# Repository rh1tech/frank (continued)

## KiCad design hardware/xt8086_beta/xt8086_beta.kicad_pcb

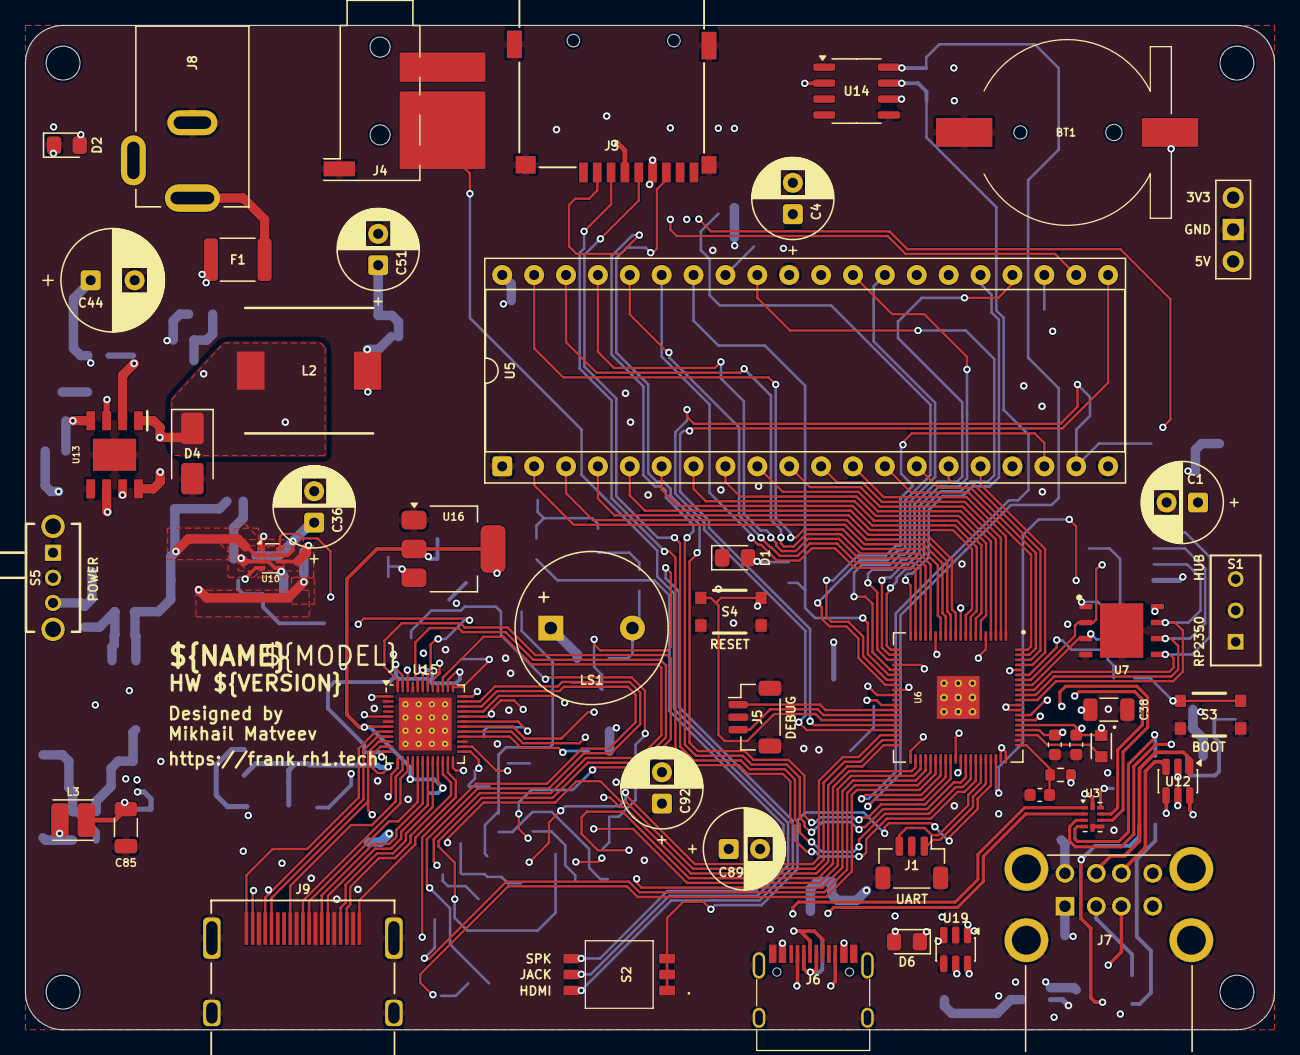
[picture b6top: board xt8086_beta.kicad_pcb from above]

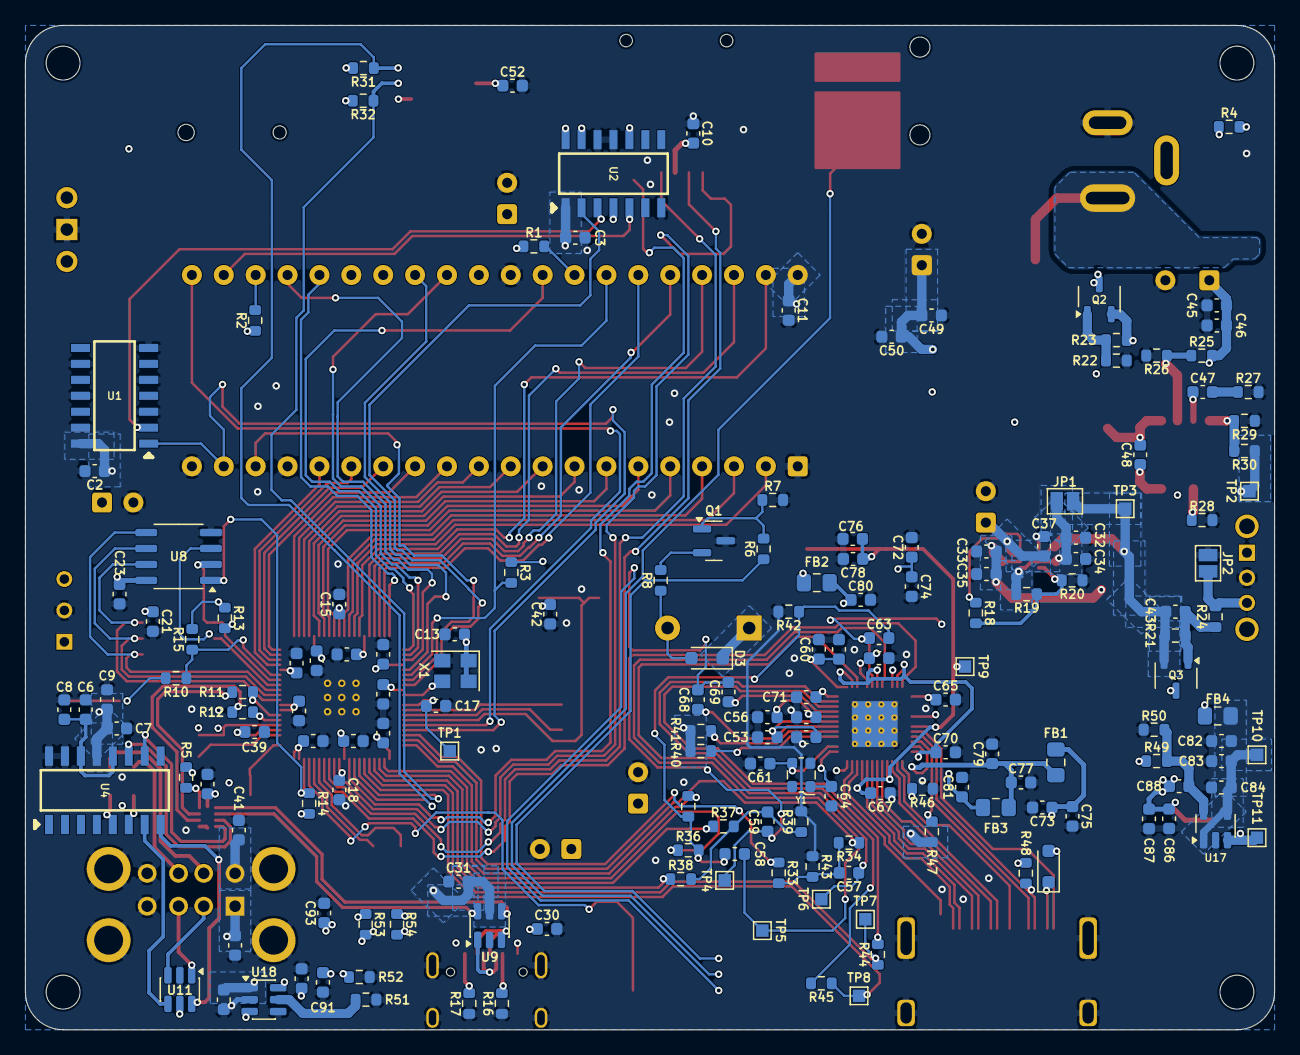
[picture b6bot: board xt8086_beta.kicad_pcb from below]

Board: 4 copper layers, 99.5 x 80.0 mm, 219 parts (167 on the bottom side), 163 nets.

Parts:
BT1: Battery_CR1220
C1, C4, C36, C89, C92: 100u; CP_Radial_D6.3mm_P2.50mm
C2, C3, C5, C8, C9, C10, C11, C13, C15, C18, C19, C20, C21, C22, C23, C24, C25, C26, C27, C28, C29, C30, C31, C32, C33, C37, C39, C46, C48, C49, C52, C57, C58, C59, C65, C66, C67, C70, C71, C74, C75, C84, C87, C93, C94: 100n; C_0603_1608Metric
C6, C43, C68, C69, C78, C79: 1u; C_0603_1608Metric
C7, C12, C14, C16, C17, C54, C56, C62: 4.7u; C_0603_1608Metric
C34, C35, C40, C41, C45, C50, C72, C73, C76, C77, C80, C81, C82, C83, C86, C90, C91: 10u; C_0603_1608Metric
C38, C85: 100u; C_1206_3216Metric
C42, C63: 1n; C_0603_1608Metric
C44: 680u; CP_Radial_D8.0mm_P3.50mm
C47: 150p; C_0603_1608Metric
C51: 220u; CP_Radial_D6.3mm_P2.50mm
C53, C55, C60: 220n; C_0603_1608Metric
C61, C64: 15p; C_0603_1608Metric
C88: 22p; C_0603_1608Metric
D1, D6: Red; LED_0805_2012Metric_Pad1.15x1.40mm_HandSolder
D2: Green; LED_0805_2012Metric_Pad1.15x1.40mm_HandSolder
D3: 1N4148; D_SOD-323
D4: SS34; D_SMA
D5: 1N5819WS; D_SOD-323
F1: 1.5A 24V; Fuse_1812_4532Metric
FB1, FB2, FB3: 220R; L_0805_2012Metric
FB4: 330R 2A; L_0805_2012Metric
H1, H2, H3, H4: Hole 2.7mm; MountingHole_2.7mm
J1: UART; JST_SH_1x03_P1.00mm_Vertical
J2: PWR; PinHeader_1x03_P2.54mm_Vertical
J3: 104031-0811; MicroSD_SMD_Long
J4: PJ-320D; AudioJack_3.5mm_PJ320D_AudioOut
J5: Debug; JST_SH_1x03_P1.00mm_Vertical
J6: USB4215-03-A; USB_C_Receptacle
J7: SS-52100-004; USB_A_Stacked
J8: DC-005-5A-2.0; BarrelJack_DC-005
J9: DC3RX19JA2; HDMI_Female
JP1: Power Debug; SolderJumper-2_P1.3mm_Open_Pad1.0x1.5mm
JP2: Force On; SolderJumper-2_P1.3mm_Open_Pad1.0x1.5mm
L1: 3.3u; L_LQH2MCN100K02L
L2: 22uH; Inductor_CDRH104RNP
L3: 2.2uH; L_Cenker_CKCS3015
LS1: Buzzer; Buzzer_12x8.5RM6.5
Q1: BC847; SOT-23
Q2, Q3: AO3401A; SOT-23-3L_AOS
R1, R2, R3, R4, R10, R46, R54: 1K; R_0603_1608Metric
R5, R7, R13, R14, R24: 10K; R_0603_1608Metric
R6, R15: 0R; R_0603_1608Metric
R8: 22R; R_0603_1608Metric
R9: 33R; R_0603_1608Metric
R11, R12: 27R; R_0603_1608Metric
R16, R17: 5.1K; R_0603_1608Metric
R18: 1M; R_0603_1608Metric
R19: 300K; R_0603_1608Metric
R20, R21, R22, R23, R25, R27, R28, R49, R51, R52, R53: 100K; R_0603_1608Metric
R26: 39K; R_0603_1608Metric
R29: 8.2K; R_0603_1608Metric
R30: 43K; R_0603_1608Metric
R31, R32, R40, R41: 4.7K; R_0603_1608Metric
R33, R35, R37: 800R; R_0603_1608Metric
R34, R36, R38: 400R; R_0603_1608Metric
R39, R42, R43: 75R; R_0603_1608Metric
R44, R45: 100R; R_0603_1608Metric
R47, R48: 2K; R_0603_1608Metric
R50: 22K; R_0603_1608Metric
S1: SS12D00; Switch_Slide_SS12D00
S2: DS05-127-2-03BK-SMT-TR; SW_DIP_DS05-127-2-03BK-SMT
S3: Boot; Button_SMD_3x4x2mm
S4: Reset; Button_SMD_3x4x2mm
S5: SK12D07VG3NS; Switch_Slide_SK12D07VG3NS
TP1: +1V1; TestPoint_Pad_1.0x1.0mm
TP2: +5V_DC; TestPoint_Pad_1.0x1.0mm
TP3: +5V_SEL; TestPoint_Pad_1.0x1.0mm
TP4: R; TestPoint_Pad_1.0x1.0mm
TP5: G; TestPoint_Pad_1.0x1.0mm
TP6: B; TestPoint_Pad_1.0x1.0mm
TP7: HS; TestPoint_Pad_1.0x1.0mm
TP8: VS; TestPoint_Pad_1.0x1.0mm
TP9: AMS_1V8; TestPoint_Pad_1.0x1.0mm
TP10: +5V_BUCK; TestPoint_Pad_1.0x1.0mm
TP11: LX; TestPoint_Pad_1.0x1.0mm
U1: SN74LS04; SOIC127P600X175-14N
U2: SN74LS74; SOIC127P600X175-14N
U3: TS3USB221RSER; Texas_R-PUQFN-N10
U4: MW7211A; SOIC127P600X175-16N
U5: 8086_Min_Mode; DIP-40_W15.24mm_Socket
U6: RP2350B; RP2350-QFN-80_10x10_P0.4mm
U7: W25Q128JVPIQ; SON127P600X500X80-9N-D
U8: ESP-PSRAM64H; SO-8
U9, U11, U12: USBLC6-2SC6; SOT-23-6
U10: TPS2116DRL; SOT-583-8
U13: MP1584EN-LF-Z; SOIC-9_P1.27mm
U14: DS3231MZ; SO-8
U15: MS9288A; QFN-48_7x7mm_P0.4mm
U16: AMS1117-1.8; SOT-223-3_TabPin2
U17: SY8089AAAC; SOT-23-5
U18, U19: CH217K; SOT-23-6
X1: ASE-12MHz; Oscillator_SMD_3225_4Pin
Y1: 24.576 MHz; Crystal_SMD_2520-4Pin

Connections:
+1V1: C14.1, C15.1, C17.1, C18.1, L1.1, TP1.1 (1_1), U6.10 (DVDD), U6.32 (DVDD), U6.51 (DVDD), U6.65 (VREG_FB)
+3V3: C5.2, C10.2, C12.1, C13.1, C19.1, C20.1, C21.1, C22.1, C23.1, C24.1, C25.1, C26.1, C27.1, C28.1, C29.1, C38.1, C39.1, C52.1, C73.1, C75.1, C85.1, C86.1, C87.1, C88.1, FB1.1, J2.3, J3.4 (VDD), L3.2, R4.2, R5.1, R9.1, R13.2, R14.2, R31.2, R32.2, R49.1, U3.10 (VCC), U6.5 (IOVDD), U6.15 (IOVDD), U6.24 (IOVDD), U6.29 (IOVDD), U6.41 (IOVDD), U6.50 (IOVDD), U6.59 (ADC_AVDD), U6.60 (IOVDD), U6.64 (VREG_VIN), U6.68 (USB_OTP_VDD), U6.69 (QSPI_IOVDD), U6.76 (IOVDD), U7.8 (VCC), U8.8 (VCC), U14.2 (VCC), X1.1 (EN), X1.4 (Vdd)
+5V_DC: C32.2, C34.2, C49.2, C50.1, C51.1, JP1.1, L2.2, R19.2, R30.1, TP2.1 (1_1), U10.3 (VIN1), U10.5 (MODE)
+5V_SEL: C31.2, C36.1, C37.1, C43.1, JP1.2, Q3.2 (S), R21.1, TP3.1 (1_1), U9.5 (VBUS), U10.2 (VOUT), U10.7 (VOUT)
/A16/GP16: U5.38 (A16/S3), U6.16 (GPIO16)
/A17/GP17: U5.37 (A17/S4), U6.17 (GPIO17)
/A18/GP18: U5.36 (A18/S5), U6.18 (GPIO18)
/A19/GP19: U5.35 (A19/S6), U6.19 (GPIO19)
/AD0/GP0: U5.16 (AD0), U6.77 (GPIO0)
/AD1/GP1: U5.15 (AD1), U6.78 (GPIO1)
/AD2/GP2: U5.14 (AD2), U6.79 (GPIO2)
/AD3/GP3: U5.13 (AD3), U6.80 (GPIO3)
/AD4/GP4: U5.12 (AD4), U6.1 (GPIO4)
/AD5/GP5: U5.11 (AD5), U6.2 (GPIO5)
/AD6/GP6: U5.10 (AD6), U6.3 (GPIO6)
/AD7/GP7: U5.9 (AD7), U6.4 (GPIO7)
/AD8/GP8: U5.8 (AD8), U6.6 (GPIO8)
/AD9/GP9: U5.7 (AD9), U6.7 (GPIO9)
/AD10/GP10: U5.6 (AD10), U6.8 (GPIO10)
/AD11/GP11: U5.5 (AD11), U6.9 (GPIO11)
/AD12/GP12: U5.4 (AD12), U6.11 (GPIO12)
/AD13/GP13: U5.3 (AD13), U6.12 (GPIO13)
/AD14/GP14: U5.2 (AD14), U6.13 (GPIO14)
/AD15/GP15: U5.39 (AD15), U6.14 (GPIO15)
/ALE/GP20: U5.25 (ALE), U6.20 (GPIO20)
/BHE/GP25: R3.2, U5.34 (~BHE/S7), U6.26 (GPIO25)
/CLK/GP29: U1.1 (1A), U5.19 (CLK), U6.37 (GPIO29)
/GP27: U2.2 (D1), U6.28 (GPIO27)
/HDMI_AUDIO: C68.2, C69.2, S2.2 (NO_1)
/INTA/GP23: U5.24 (~INTA), U6.23 (GPIO23)
/INTR/GP26: U5.18 (INTR), U6.27 (GPIO26)
/JACK_IN: J4.R, J4.T, S2.4 (NO_2)
/MIO/GP24: U5.28 (M/~IO), U6.25 (GPIO24)
/MN/MX: R1.2, U5.33 (MN/~MX)
/Micro SD/CDDAT3: J3.2 (DAT3/CD), U6.52 (GPIO41_ADC1)
/Micro SD/CLK: J3.5 (CLK), U6.53 (GPIO42_ADC2)
/Micro SD/CMD: J3.3 (CMD), U6.54 (GPIO43_ADC3)
/Micro SD/DAT0: J3.7 (DAT0), U6.49 (GPIO40_ADC0)
/RD/GP21: U5.32 (~RD), U6.21 (GPIO21)
/READY: U2.5 (Q1), U5.22 (READY)
/RESET/GP28: U5.21 (RESET), U6.36 (GPIO28)
/RP2350B/DM: R12.1, U3.7 (D-)
/RP2350B/DP: R11.1, U3.8 (D+)
/RP2350B/GP30: R33.1, U6.38 (GPIO30)
/RP2350B/GP31: R34.1, U6.39 (GPIO31)
/RP2350B/GP32: R35.1, U6.40 (GPIO32)
/RP2350B/GP33: R36.1, U6.42 (GPIO33)
/RP2350B/GP34: R37.1, U6.43 (GPIO34)
/RP2350B/GP35: R38.1, U6.44 (GPIO35)
/RP2350B/GP36: R44.1, TP7.1 (1_1), U6.45 (GPIO36)
/RP2350B/GP37: R45.1, TP8.1 (1_1), U6.46 (GPIO37)
/RP2350B/GP38: R32.1, U6.47 (GPIO38), U14.7 (SDA)
/RP2350B/GP39: R31.1, U6.48 (GPIO39), U14.8 (SCL)
/RP2350B/GP47: R14.1, U6.58 (GPIO47_ADC7), U8.1 (~CE)
/RP2350B/QSPI_SCLK: U6.71 (QSPI_SCLK), U7.6 (CLK), U8.6 (SCLK)
/RP2350B/QSPI_SD0: U6.72 (QSPI_SD0), U7.5 (DI_(IO0)), U8.5 (SI/SIO)
/RP2350B/QSPI_SD1: U6.74 (QSPI_SD1), U7.2 (DO_(IO1)), U8.2 (SO/SIO)
/RP2350B/QSPI_SD2: U6.73 (QSPI_SD2), U7.3 (~WP_(IO2)), U8.3 (SIO2)
/RP2350B/QSPI_SD3: U6.70 (QSPI_SD3), U7.7 (~HOLD_OR_/RESET_(IO3)), U8.7 (SIO3)
/RP2350B/QSPI_SS: R10.1, R15.1, U6.75 (QSPI_SS)
/RP2350B/Reset/RESET: C42.2, S4.2, S4.4, U6.35 (RUN)
/RP2350B/SWCLK: J5.3, U6.33 (SWCLK)
/RP2350B/SWD: J5.1, U6.34 (SWD)
/RP2350B/VREG_AVDD: C16.1, R9.2, U6.61 (VREG_AVDD)
/RP2350B/VREG_LX: L1.2, U6.63 (VREG_LX)
/RP2350B/XIN: U6.30 (XIN), X1.3 (OUT)
/RP2350B/~USB_BOOT: R10.2, S3.2, S3.4
/SPEAKER: S2.1 (COM_1), S2.3 (COM_2), S2.5 (COM_3), U6.57 (GPIO46_ADC6)
/SPK_IN: R6.1, S2.6 (NO_3)
/TEST: R2.2, U5.23 (~TEST)
/UART0_RX: J1.3, U6.56 (GPIO45_ADC5)
/UART0_TX: J1.1, U6.55 (GPIO44_ADC4)
/USB, Power/3V3 Buck/+5V_BUCK: C82.1, C83.1, C84.1, FB4.2, TP10.1 (1_1), U17.1 (EN), U17.4 (IN)
/USB, Power/3V3 Buck/FB: C88.2, R49.2, R50.1, U17.5 (FB)
/USB, Power/ST: R18.1, U10.8 (ST)
/USB, Power/SW: R5.2, S1.1, U3.9 (S)
/USB, Power/UA1M: U4.7 (DM3), U11.4 (I/O2)
/USB, Power/UA1P: U4.8 (DP3), U11.6 (I/O1)
/USB, Power/UA2M: U4.5 (DM2), U12.6 (I/O1)
/USB, Power/UA2P: U4.6 (DP2), U12.4 (I/O2)
/USB, Power/UAM: U3.4 (2D-), U4.10 (DMU)
/USB, Power/UAP: U3.3 (2D+), U4.11 (DPU)
/USB, Power/UCM: U3.2 (1D-), U9.6 (I/O1)
/USB, Power/UCP: U3.1 (1D+), U9.4 (I/O2)
/USB, Power/USB Hub/VD33: C6.1, C8.1, U4.12 (VD33), U4.14 (VD3)
/USB, Power/USB-A Port Power/USB_OC: D6.1 (K), R53.2, U18.3 (FLAG#), U19.3 (FLAG#)
/USB, Power/VBUS_P1: C40.1, C94.1, J7.1 (VBUS1), U18.1 (VOUT)
/USB, Power/VBUS_P2: C41.1, C93.1, J7.5 (VBUS2), U19.1 (VOUT)
/USB, Power/VBUS_USB: C30.1, C33.2, C35.2, J6.2 (VBUS), J6.11 (VBUS), U10.6 (VIN2)
/Video/ALIN: C68.1, U15.30 (ALIN)
/Video/AMS_1V8: C67.1, C76.1, C78.1, FB2.1, TP9.1 (1_1), U15.7 (AVDD18), U15.16 (AVDD18), U15.21 (AVDD18), U16.2 (VO)
/Video/AMS_1V8A: C65.1, C66.1, C80.1, FB2.2, U15.1 (AVDD18_ADC), U15.41 (AVDD18_ADC), U15.46 (AVDD18_ADC)
/Video/AMS_3V3: C71.1, C72.1, C74.1, C77.1, C79.1, FB1.2, FB3.1, U15.5 (DVDD33), U15.11 (DVDD33), U15.24 (DVDD33), U15.36 (DVDD33), U16.3 (VI)
/Video/AMS_3V3A: C70.1, C81.1, FB3.2, U15.12 (AVDD33), U15.38 (AVDD33), U15.43 (AVDD33), U15.47 (AVDD33)
/Video/ARIN: C69.1, U15.33 (ARIN)
/Video/B: C57.1, TP6.1 (1_1), U15.39 (B/Pb)
/Video/DCCSCL: J9.15 (SCL), R47.1, U15.10 (DCCSCL)
/Video/DDCSDA: J9.16 (SDA), R48.1, U15.9 (DDCSDA)
/Video/G: C58.1, TP5.1 (1_1), U15.44 (G/Y)
/Video/HPDT: J9.19 (HOT_PLUG_DET), U15.8 (HotPlugDetect)
/Video/R: C59.1, TP4.1 (1_1), U15.48 (R/Pr)
/Video/SCL: R40.1, U15.28 (SCL)
/Video/SDA: R41.1, U15.29 (SDA)
/Video/SOG_G: C58.2, C63.2, R35.2, R36.2, R42.1
/Video/TMDS_CLK+: J9.10 (CLKP), U15.15 (TMDS_CLK+)
/Video/TMDS_CLK-: J9.12 (CLKN), U15.14 (TMDS_CLK-)
/Video/TMDS_D0+: J9.7 (D0P), U15.18 (TMDS-D0+)
/Video/TMDS_D0-: J9.9 (D0N), U15.17 (TMDS_D0-)
/Video/TMDS_D1+: J9.4 (D1P), U15.20 (TMDS_D1+)
/Video/TMDS_D1-: J9.6 (D1N), U15.19 (TMDS_D1-)
/Video/TMDS_D2+: J9.1 (D2P), U15.23 (TMDS_D2+)
/Video/TMDS_D2-: J9.3 (D2N), U15.22 (TMDS_D2-)
/WR/GP22: U5.29 (~WR), U6.22 (GPIO22)
GND: BT1.2 (-), C1.2, C2.2, C3.2, C4.2, C5.1, C6.2, C7.2, C8.2, C9.2, C10.1, C11.2, C12.2, C13.2, C14.2, C15.2, C16.2, C17.2, C18.2, C19.2, C20.2, C21.2, C22.2, C23.2, C24.2, C25.2, C26.2, C27.2, C28.2, C29.2, C30.2, C31.1, C32.1, C33.1, C34.1, C35.1, C36.2, C37.2, C38.2, C39.2, C40.2, C41.2, C42.1, C44.2, C45.2, C46.2, C49.1, C50.2, C51.2, C52.2, C53.2, C54.2, C55.2, C56.2, C60.2, C61.2, C62.2, C64.2, C65.2, C66.2, C67.2, C70.2, C71.2, C72.2, C73.2, C74.2, C75.2, C76.2, C77.2, C78.2, C79.2, C80.2, C81.2, C82.2, C83.2, C84.2, C85.2, C86.2, C87.2, C89.2, C90.2, C91.2, C92.2, C93.2, C94.2, D1.1 (K), D2.1 (K), D4.2 (A), J1.2, J2.2, J3.6 (VSS), J3.SH (SHIELD), J4.S, J5.2, J6.1 (GND), J6.12 (GND), J6.13 (SHIELD), J7.4 (GND1), J7.8 (GND2), J7.SH (Shield), J8.2, J9.2 (G_D2), J9.5 (G_D1), J9.8 (G_D0), J9.11 (G_CLK), J9.17 (G_DDC/CEC), J9.20 (SHIELD1), J9.21 (SHIELD2), J9.22 (SHIELD3), J9.23 (SHIELD4), JP2.1 (A), Q1.3 (E), R7.2, R16.1, R17.1, R20.1, R22.2, R26.2, R27.2, R28.2, R29.1, R39.2, R42.2, R43.2, R46.1, R50.2, R51.2, R52.2, S1.2, S3.1, S3.3, S4.1, S4.3, S5.2, U1.3 (2A), U1.5 (3A), U1.7 (GND), U1.9 (4A), U1.11 (5A), U1.13 (6A), U2.7 (GND), U2.11 (CLK2), U2.12 (D2), U3.5 (GND), U3.6 (~OE), U4.15 (GND), U4.16 (GND), U5.1 (GND), U5.17 (NMI), U5.20 (GND), U5.31 (HOLD), U6.62 (VREG_PGND), U6.81 (GND), U7.4 (GND_1), U7.9 (GND_2), U8.4 (VSS), U9.2 (GND), U10.1 (GND), U11.2 (GND), U12.2 (GND), U13.5 (GND), U13.9 (EP), U14.5 (GND), U15.2 (GND), U15.6 (GND), U15.27 (GND), U15.40 (GND), U15.45 (GND), U15.49 (EP), U16.1 (GND), U17.2 (GND), U18.2 (GND), U18.4 (EN#), U19.2 (GND), U19.4 (EN#), X1.2 (GND), Y1.2 (GND), Y1.4 (GND)
unnamed: BT1.1 (+), U14.6 (VBAT)
unnamed: C47.2, R27.1
unnamed: C57.2, R33.2, R34.2, R43.1
unnamed: C59.2, R37.2, R38.2, R39.1
unnamed: D1.2 (A), R3.1
unnamed: D2.2 (A), R4.1
unnamed: D3.2 (A), LS1.2 (-), R8.1
unnamed: C48.2, D4.1 (K), L2.1, U13.1 (SW)
unnamed: D5.1 (K), J9.18 (+5V)
unnamed: D6.2 (A), R54.2
unnamed: F1.1, J8.1
unnamed: J6.4 (CC1), R16.2
unnamed: J6.10 (CC2), R17.2
unnamed: J6.5 (DN2), J6.7 (DN1), U9.1 (I/O1)
unnamed: J6.6 (DP1), J6.8 (DP2), U9.3 (I/O2)
unnamed: J7.3 (D1+), U11.1 (I/O1)
unnamed: J7.2 (D1-), U11.3 (I/O2)
unnamed: J7.7 (D2+), U12.3 (I/O2)
unnamed: J7.6 (D2-), U12.1 (I/O1)
unnamed: JP2.2 (B), R24.2, S5.3
unnamed: Q1.2 (B), R6.2, R7.1
unnamed: Q1.1 (C), R8.2
unnamed: F1.2, Q2.3 (D)
unnamed: Q2.1 (G), R22.1, R23.1
unnamed: C44.1, C45.1, C46.1, Q2.2 (S), R23.2, R25.2, U13.7 (VIN)
unnamed: C43.2, Q3.1 (G), R21.2, R24.1
unnamed: U1.2 (1Y), U2.3 (CLK1)
unnamed: R12.2, U6.66 (USB_DM)
unnamed: R11.2, U6.67 (USB_DP)
unnamed: R13.1, R15.2, U7.1 (~CS)
unnamed: R18.2, R19.1, R20.2, U10.4 (PR1)
unnamed: C48.1, U13.8 (BST)
unnamed: C47.1, U13.3 (COMP)
unnamed: R25.1, R26.1, U13.2 (EN)
unnamed: R29.2, R30.2, U13.4 (FB)
unnamed: R28.1, U13.6 (FREQ)
unnamed: R44.2, U15.34 (HSIN)
unnamed: C60.1, C62.1, U15.37 (REFP)
unnamed: C53.1, C54.1, U15.31 (REFQ0)
unnamed: C55.1, C56.1, U15.32 (REFQ1)
unnamed: C63.1, U15.42 (SOG/Y)
unnamed: R46.2, U15.13 (SWREF1k)
unnamed: R45.2, U15.35 (VSIN)
unnamed: C64.1, U15.25 (XTI), Y1.1 (OSC)
unnamed: C61.1, U15.26 (XTO), Y1.3 (OSC)
unnamed: L3.1, TP11.1 (1_1), U17.3 (LX)
unnamed: R51.1, U18.5 (ISET)
unnamed: R52.1, U19.5 (ISET)
VBUS: C1.1, C2.1, C3.1, C4.1, C7.1, C9.1, C11.1, C89.1, C90.1, C91.1, C92.1, D3.1 (K), D5.2 (A), FB4.1, J2.1, LS1.1 (+), Q3.3 (D), R1.1, R2.1, R40.2, R41.2, R47.2, R48.2, R53.1, R54.1, U1.14 (VCC), U2.1 (CLR1), U2.4 (PR1), U2.10 (PR2), U2.13 (CLR2), U2.14 (VCC), U4.13 (VDD5), U5.40 (VCC), U11.5 (VBUS), U12.5 (VBUS), U18.6 (VIN), U19.6 (VIN)

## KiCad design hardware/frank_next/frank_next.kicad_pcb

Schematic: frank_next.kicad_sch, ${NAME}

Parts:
H1, H2, H3, H4: MountingHole; MountingHole_2.5mm_Pad_Via
JP1: USB_SEL Debug; SolderJumper-2_P1.3mm_Open_RoundedPad1.0x1.5mm
JP2: DS05-127-2-02BK-SMT-TR; SW_DS05-127-2-02BK-SMT-TR; Mouser Part Number 490-DS05127202BK-STR
JP3: UART SEL Debug; SolderJumper-2_P1.3mm_Open_RoundedPad1.0x1.5mm
R1, R3: 33R; R_0603_1608Metric; LCSC C23140
R2: 10K; R_0603_1608Metric; LCSC C2906982

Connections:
+3V3: R2.2; also elsewhere on the board
/RP2350A/GPIO9: R1.2; also elsewhere on the board
/RP2350B/GPIO38: R3.1; also elsewhere on the board
/RP2350/28B/9A/CLK: R1.1; also elsewhere on the board
/RP2350/38B/19A/CLK: R3.2; also elsewhere on the board
/RP2350/43B/RUNA/SR: R2.1; also elsewhere on the board
/UART_SEL: JP2.3 (COM_2), JP3.2 (B); also elsewhere on the board
/USB_SEL: JP1.2 (B), JP2.1 (COM_1); also elsewhere on the board
GND: H1.1 (1_1), H2.1 (1_1), H3.1 (1_1), H4.1 (1_1), JP1.1 (A), JP2.2 (NO_1), JP2.4 (NO_2), JP3.1 (A); also elsewhere on the board

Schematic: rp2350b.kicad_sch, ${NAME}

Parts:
C1, C2, C7, C10, C11, C12, C13, C14, C15, C16, C17, C18, C19: 100nF; C_0603_1608Metric; LCSC C14663
C3, C4, C8, C9: 4.7uF; C_0603_1608Metric; LCSC C5360844
C5, C6: 15pF; C_0603_1608Metric; LCSC C1644
J1: Debug; JST_SH_1x03_P1.00mm_Vertical; LCSC C160389
J2: UART; JST_SH_1x03_P1.00mm_Vertical; LCSC C160389
L1: 3.3µH; L_AOTA-B201610_2.0x1.6mm; LCSC C98035
R4, R5: 10K; R_0603_1608Metric; LCSC C2906982
R6: 33R; R_0603_1608Metric; LCSC C23140
R7, R9: 1K; R_0603_1608Metric; LCSC C21190
R8: 0R; R_0603_1608Metric; LCSC C21189
R10, R11, R12, R13: 100R; R_0603_1608Metric; LCSC C21190
R14, R15: 27R; R_0603_1608Metric; LCSC C25190
R16, R17: 330R; R_0603_1608Metric
S1: RP Boot; Button_SMD_3x4x2mm; Mouser Part Number 611-KMR221G-LFS; LCSC C36498961
S2: RP Reset; Button_SMD_3x4x2mm; Mouser Part Number 611-KMR221G-LFS; LCSC C36498961
U1: APS6404L-3SQR-ZR; PSON50P200X300X50-9N; PARTREV 2.3; LCSC C3040877
U2: W25Q128JVPIQ; WSON-8-1EP_6x5mm_P1.27mm_EP3.45x4.35mm; Mouser Part Number 454-W25Q128JVPIQ; LCSC C190862
U3: RP2350B; RP2350-QFN-80_10x10_P0.4mm; LCSC C42415655
Y1: 12 MHz; Crystal_SMD_3225-4Pin_3.2x2.5mm; LCSC C9002

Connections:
+1V1: C4.1, C7.1, C9.1, C10.1, L1.1, U3.10 (DVDD), U3.32 (DVDD), U3.51 (DVDD), U3.65 (VREG_FB)
+3V3: C1.1, C2.2, C3.1, C11.1, C12.1, C13.1, C14.1, C15.1, C16.1, C17.1, C18.1, C19.1, R4.2, R5.2, R6.1, U1.8 (VDD), U2.8 (VCC), U3.5 (IOVDD), U3.15 (IOVDD), U3.24 (IOVDD), U3.29 (IOVDD), U3.41 (IOVDD), U3.50 (IOVDD), U3.59 (ADC_AVDD), U3.60 (IOVDD), U3.64 (VREG_VIN), U3.68 (USB_OTP_VDD), U3.69 (QSPI_IOVDD), U3.76 (IOVDD); also elsewhere on the board
/GPIO2/SDA: U3.79 (GPIO2); also elsewhere on the board
/GPIO3/SCL: U3.80 (GPIO3); also elsewhere on the board
/GPIO8/MCLK: U3.6 (GPIO8); also elsewhere on the board
/GPIO9/BCLK: U3.7 (GPIO9); also elsewhere on the board
/GPIO10/WCLK: U3.8 (GPIO10); also elsewhere on the board
/GPIO11/DIN: U3.9 (GPIO11); also elsewhere on the board
/GPIO12/CLKN: U3.11 (GPIO12); also elsewhere on the board
/GPIO13/CLKP: U3.12 (GPIO13); also elsewhere on the board
/GPIO14/D0N: U3.13 (GPIO14); also elsewhere on the board
/GPIO15/D0P: U3.14 (GPIO15); also elsewhere on the board
/GPIO16/D1N: U3.16 (GPIO16); also elsewhere on the board
/GPIO17/D1P: U3.17 (GPIO17); also elsewhere on the board
/GPIO18/D2N: U3.18 (GPIO18); also elsewhere on the board
/GPIO19/D2P: U3.19 (GPIO19); also elsewhere on the board
/RP2350B/BOOT: R7.2, S1.1, S1.3
/RP2350B/D+: R14.1; also elsewhere on the board
/RP2350B/D-: R15.1; also elsewhere on the board
/RP2350B/GPIO38: R12.2; also elsewhere on the board
/RP2350B/GPIO44: U3.55 (GPIO44_ADC4); also elsewhere on the board
/RP2350B/GPIO47: R4.1, U1.1 (~CE), U3.58 (GPIO47_ADC7)
/RP2350B/QSPI_SCLK: U1.6 (SCLK), U2.6 (CLK), U3.71 (QSPI_SCLK)
/RP2350B/QSPI_SD0: U1.5 (SI/SIO(0)), U2.5 (DI_(IO0)), U3.72 (QSPI_SD0)
/RP2350B/QSPI_SD1: U1.2 (SO/SIO(1)), U2.2 (DO_(IO1)), U3.74 (QSPI_SD1)
/RP2350B/QSPI_SD2: U1.3 (SIO(2)), U2.3 (~WP_(IO2)), U3.73 (QSPI_SD2)
/RP2350B/QSPI_SD3: U1.7 (SIO(3)), U2.7 (~HOLD_OR_/RESET_(IO3)), U3.70 (QSPI_SD3)
/RP2350B/QSPI_SS: R7.1, R8.1, U3.75 (QSPI_SS)
/RP2350B/RUN: S2.1, S2.3, U3.35 (RUN)
/RP2350B/SWCLK: J1.3, U3.33 (SWCLK)
/RP2350B/SWD: J1.1, U3.34 (SWD)
/RP2350B/VREG_AVDD: C8.1, R6.2, U3.61 (VREG_AVDD)
/RP2350B/VREG_LX: L1.2, U3.63 (VREG_LX)
/RP2350B/XIN: C5.1, U3.30 (XIN), Y1.3
/RP2350B/XOUT: R9.2, U3.31 (XOUT)
/RP2350/20B/1A/D0: U3.20 (GPIO20); also elsewhere on the board
/RP2350/21B/2A/D1: U3.21 (GPIO21); also elsewhere on the board
/RP2350/22B/3A/D2: U3.22 (GPIO22); also elsewhere on the board
/RP2350/23B/4A/D3: U3.23 (GPIO23); also elsewhere on the board
/RP2350/24B/5A/D4: U3.25 (GPIO24); also elsewhere on the board
/RP2350/25B/6A/D5: U3.26 (GPIO25); also elsewhere on the board
/RP2350/26B/7A/D6: U3.27 (GPIO26); also elsewhere on the board
/RP2350/27B/8A/D7: U3.28 (GPIO27); also elsewhere on the board
/RP2350/28B/9A/CLK: R10.2; also elsewhere on the board
/RP2350/29B/10A/VALID: R11.2; also elsewhere on the board
/RP2350/30B/11A/D0: U3.38 (GPIO30); also elsewhere on the board
/RP2350/31B/12A/D1: U3.39 (GPIO31); also elsewhere on the board
/RP2350/32B/13A/D2: U3.40 (GPIO32); also elsewhere on the board
/RP2350/33B/14A/D3: U3.42 (GPIO33); also elsewhere on the board
/RP2350/34B/15A/D4: U3.43 (GPIO34); also elsewhere on the board
/RP2350/35B/16A/D5: U3.44 (GPIO35); also elsewhere on the board
/RP2350/36B/17A/D6: U3.45 (GPIO36); also elsewhere on the board
/RP2350/37B/18A/D7: U3.46 (GPIO37); also elsewhere on the board
/RP2350/39B/20A/VALID: R13.2; also elsewhere on the board
/RP2350/40B/21A/FS: U3.49 (GPIO40_ADC0); also elsewhere on the board
/RP2350/41B/22A/DB_MS: U3.52 (GPIO41_ADC1); also elsewhere on the board
/RP2350/42B/23A/DB_SM: U3.53 (GPIO42_ADC2); also elsewhere on the board
/RP2350/43B/RUNA/SR: U3.54 (GPIO43_ADC3); also elsewhere on the board
/RP_RX: R17.2, U3.56 (GPIO45_ADC5); also elsewhere on the board
/RP_TX: R16.2, U3.57 (GPIO46_ADC6); also elsewhere on the board
/SD/CD_DAT3/GPIO7: U3.4 (GPIO7); also elsewhere on the board
/SD/CLK/GPIO1: U3.78 (GPIO1); also elsewhere on the board
/SD/CMD/GPIO0: U3.77 (GPIO0); also elsewhere on the board
/SD/DAT0/GPIO4: U3.1 (GPIO4); also elsewhere on the board
/SD/DAT1/GPIO5: U3.2 (GPIO5); also elsewhere on the board
/SD/DAT2/GPIO6: U3.3 (GPIO6); also elsewhere on the board
GND: C1.2, C2.1, C3.2, C4.2, C5.2, C6.2, C7.2, C8.2, C9.2, C10.2, C11.2, C12.2, C13.2, C14.2, C15.2, C16.2, C17.2, C18.2, C19.2, J1.2, J2.2, S1.2, S1.4, S2.2, S2.4, U1.4 (VSS), U1.9 (EXP), U2.4 (GND_1), U2.9 (GND_2), U3.62 (VREG_PGND), U3.81 (GND), Y1.2, Y1.4; also elsewhere on the board
unnamed: C6.1, R9.1, Y1.1
unnamed: J2.1, R16.1
unnamed: J2.3, R17.1
unnamed: R5.1, R8.2, U2.1 (~CS)
unnamed: R10.1, U3.36 (GPIO28)
unnamed: R11.1, U3.37 (GPIO29)
unnamed: R12.1, U3.47 (GPIO38)
unnamed: R13.1, U3.48 (GPIO39)
unnamed: R15.2, U3.66 (USB_DM)
unnamed: R14.2, U3.67 (USB_DP)

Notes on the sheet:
Close to RP2350
68+69

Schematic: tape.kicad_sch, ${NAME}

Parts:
C67, C68: 100nF; C_0603_1608Metric; LCSC C14663
D3: 1N4148; D_SOD-323; LCSC C2128
J9: PJ-320D; AudioJack_3.5mm_PJ320D_TapeIn; LCSC C431535
Q2, Q3: BC850; SOT-23; LCSC C503377
R44: 100R; R_0603_1608Metric; LCSC C22775
R45, R46, R47: 10K; R_0603_1608Metric; LCSC C2906982
R48: 1K; R_0603_1608Metric; LCSC C21190

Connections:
+3V3: C68.2, R46.1, R48.1; also elsewhere on the board
/RP2350B/GPIO44: Q3.3 (C), R48.2; also elsewhere on the board
/Tape/TAPE: C67.1, J9.T, R44.1
GND: C68.1, J9.S, Q2.2 (E), Q3.2 (E), R44.2; also elsewhere on the board
unnamed: C67.2, R45.1
unnamed: D3.2 (A), Q2.3 (C), R46.2, R47.1
unnamed: D3.1 (K), Q2.1 (B), R45.2
unnamed: Q3.1 (B), R47.2

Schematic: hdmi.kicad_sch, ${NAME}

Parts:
C20: 100nF; C_0603_1608Metric; LCSC C14663
D1: 1N5819WS; D_SOD-323; LCSC C191023
J3: DC3RX19JA2; HDMI_Female
RN1, RN2: 270R; R_Array_4x0603; LCSC C1731063

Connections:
/GPIO12/CLKN: RN1.4 (R4.1); also elsewhere on the board
/GPIO13/CLKP: RN1.3 (R3.1); also elsewhere on the board
/GPIO14/D0N: RN1.2 (R2.1); also elsewhere on the board
/GPIO15/D0P: RN1.1 (R1.1); also elsewhere on the board
/GPIO16/D1N: RN2.4 (R4.1); also elsewhere on the board
/GPIO17/D1P: RN2.3 (R3.1); also elsewhere on the board
/GPIO18/D2N: RN2.2 (R2.1); also elsewhere on the board
/GPIO19/D2P: RN2.1 (R1.1); also elsewhere on the board
GND: C20.2, J3.2 (G_D2), J3.5 (G_D1), J3.8 (G_D0), J3.11 (G_CLK), J3.17 (G_DDC/CEC), J3.20 (SHIELD1), J3.21 (SHIELD2), J3.22 (SHIELD3), J3.23 (SHIELD4); also elsewhere on the board
unnamed: C20.1, D1.1 (K), J3.18 (+5V)
unnamed: J3.12 (CLKN), RN1.5 (R4.2)
unnamed: J3.10 (CLKP), RN1.6 (R3.2)
unnamed: J3.9 (D0N), RN1.7 (R2.2)
unnamed: J3.7 (D0P), RN1.8 (R1.2)
unnamed: J3.6 (D1N), RN2.5 (R4.2)
unnamed: J3.4 (D1P), RN2.6 (R3.2)
unnamed: J3.3 (D2N), RN2.7 (R2.2)
unnamed: J3.1 (D2P), RN2.8 (R1.2)
VBUS: D1.2 (A); also elsewhere on the board

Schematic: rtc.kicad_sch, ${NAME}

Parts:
BT1: CR1220; Battery_CR1220; Manufacturer_Part_Number 1174; LCSC C5199899
C69, C70: 100nF; C_0603_1608Metric; LCSC C14663
U11: DS3231MZ; SO-8_3.9x4.9mm_P1.27mm; LCSC C107410

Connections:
+3V3: C70.1, U11.2 (VCC); also elsewhere on the board
/GPIO2/SDA: U11.7 (SDA); also elsewhere on the board
/GPIO3/SCL: U11.8 (SCL); also elsewhere on the board
GND: BT1.2 (-), C69.1, C70.2, U11.5 (GND); also elsewhere on the board
unnamed: BT1.1 (+), C69.2, U11.6 (VBAT)

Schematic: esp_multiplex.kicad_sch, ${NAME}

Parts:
C100: 100nF; C_0603_1608Metric
R67, R68, R69: 10K; R_0603_1608Metric
U26: 74HC4052BQ; 74HC4052BQ115; Mouser Part Number 771-HC4052BQ115

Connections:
+3V3: C100.1, R67.1, R68.1, R69.1, U26.16 (VCC_1); also elsewhere on the board
/ESP8266/RX: U26.3 (2Z); also elsewhere on the board
/ESP8266/TX: U26.13 (1Z); also elsewhere on the board
/RP_RX: R67.2, U26.14 (1Y1); also elsewhere on the board
/RP_TX: U26.5 (2Y1); also elsewhere on the board
/TTL_RXD: R69.2, U26.12 (1Y0); also elsewhere on the board
/TTL_TXD: U26.1 (2Y0); also elsewhere on the board
/UART_SEL: R68.2, U26.10 (S0); also elsewhere on the board
GND: C100.2, U26.2 (2Y2), U26.4 (2Y3), U26.6 (~E), U26.7 (VEE), U26.8 (GND), U26.9 (S1), U26.11 (1Y3), U26.15 (1Y2); also elsewhere on the board

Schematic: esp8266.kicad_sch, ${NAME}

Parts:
AE1: Antenna_Shield; Antenna_2.4GHz
C53: 1u; C_0603_1608Metric
C54: 1.5pF; C_0603_1608Metric
C55: 2.4pF; C_0603_1608Metric
C56, C61, C62, C63, C64, C65, C66: 100nF; C_0603_1608Metric
C57, C58: 15p; C_0603_1608Metric
C59: 10u; C_0603_1608Metric
C60: 100n; C_0603_1608Metric
L4: 3nH; L_0603_1608Metric
Q1: UMH3N; SOT-363
R36, R37: 12K; R_0603_1608Metric
R38, R41, R42, R43: 10K; R_0603_1608Metric
R39, R40: 330R; R_0603_1608Metric
S5: ESP Reset; Button_SMD_3x4x2mm
S6: ESP Flash; Button_SMD_3x4x2mm; Mouser Part Number 611-KMR221G-LFS
U9: ESP8266EX; QFN-32-1EP_5x5mm_P0.5mm_EP3.45x3.45mm
U10: W25Q16JVSSIQ; SOIC-8
Y3: 26 MHz Passive; Crystal_SMD_3225-4Pin_3.2x2.5mm

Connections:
+3V3: C59.2, C60.2, C61.1, C62.1, C63.1, C64.1, C65.1, C66.1, R36.2, R38.1, R42.1, R43.1, U9.1 (VDDA), U9.3 (VDD3P3), U9.4 (VDD3P3), U9.11 (VDDPST), U9.17 (VDDPST), U9.29 (VDDD), U9.30 (VDDA), U10.8 (VCC); also elsewhere on the board
/ESP8266/ANT: AE1.1 (A), C55.1, L4.1
/ESP8266/GPIO0: Q1.3 (C2), R43.2, S6.1, S6.3, U9.15 (GPIO0)
/ESP8266/GPIO9: U9.18 (SDIO_DATA_2), U10.7 (HOLD#)
/ESP8266/GPIO10: U9.19 (SDIO_DATA_3), U10.3 (WP#)
/ESP8266/RST: C53.1, Q1.6 (C1), R36.1, S5.1, S5.3, U9.32 (~EXT_RSTB)
/ESP8266/RX: R39.1; also elsewhere on the board
/ESP8266/SD_CLK: U9.21 (SDIO_CLK), U10.6 (SCLK)
/ESP8266/SD_CMD: U9.20 (SDIO_CMD), U10.1 (CS#)
/ESP8266/SD_D0: U9.22 (SDIO_DATA_0), U10.2 (SO/SIO1)
/ESP8266/SD_D1: U9.23 (SDIO_DATA_1), U10.5 (SI/SIO0)
/ESP8266/TX: R40.1; also elsewhere on the board
/ESP8266/XIN: C58.1, U9.28 (XTAL_IN), Y3.1
/ESP8266/XOUT: C57.1, U9.27 (XTAL_OUT), Y3.3
/ESP_DTR: Q1.2 (B1), Q1.4 (E2); also elsewhere on the board
/ESP_RTS: Q1.1 (E1), Q1.5 (B2); also elsewhere on the board
GND: AE1.2 (Shield), C53.2, C54.2, C55.2, C56.2, C57.2, C58.2, C59.1, C60.1, C61.2, C62.2, C63.2, C64.2, C65.2, C66.2, R37.2, R41.1, S5.2, S5.4, S6.2, S6.4, U9.33 (GND), U10.4 (GND), Y3.2, Y3.4; also elsewhere on the board
unnamed: C56.1, R38.2, U9.7 (CHIP_PU)
unnamed: R42.2, U9.14 (GPIO2)
unnamed: C54.1, L4.2, U9.2 (LNA)
unnamed: R41.2, U9.13 (MTDO)
unnamed: R37.1, U9.31 (RES12K)
unnamed: R39.2, U9.25 (U0RXD)
unnamed: R40.2, U9.26 (U0TXD)

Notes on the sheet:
VDDD 29
U9 VCC
VDDA 30
C58 10u + C59 100n serve U10.3 / U10.4 VDD3P3 (RF supply)
ESP8266 decoupling - place each cap directly at the U10 pin named below
VDDPST 17
VDDPST 11
VDDA 1

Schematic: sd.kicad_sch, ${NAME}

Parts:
C39: 10uF; C_0603_1608Metric; LCSC C96446
C40: 100nF; C_0603_1608Metric; LCSC C14663
J6: 104031-0811; MicroSD_SMD_Long; LCSC C585350
R28, R29, R30, R31, R32: 10K; R_0603_1608Metric; LCSC C2906982

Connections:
+3V3: C39.2, C40.2, J6.4 (VDD), R28.1, R29.1, R30.1, R31.2, R32.1; also elsewhere on the board
/SD/CD_DAT3/GPIO7: J6.2 (DAT3/CD), R28.2; also elsewhere on the board
/SD/CLK/GPIO1: J6.5 (CLK); also elsewhere on the board
/SD/CMD/GPIO0: J6.3 (CMD), R29.2; also elsewhere on the board
/SD/DAT0/GPIO4: J6.7 (DAT0), R30.2; also elsewhere on the board
/SD/DAT1/GPIO5: J6.8 (DAT1), R32.2; also elsewhere on the board
/SD/DAT2/GPIO6: J6.1 (DAT2), R31.1; also elsewhere on the board
GND: C39.1, C40.1, J6.6 (VSS), J6.SH (SHIELD); also elsewhere on the board

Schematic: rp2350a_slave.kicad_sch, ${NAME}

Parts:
C21, C26, C29, C30, C31, C32, C33, C34, C35, C36, C37, C38: 100nF; C_0603_1608Metric; LCSC C14663
C22, C25, C27, C28: 4.7uF; C_0603_1608Metric; LCSC C5360844
C23, C24: 15pF; C_0603_1608Metric; LCSC C1644
D2: 1N5819WS; D_SOD-323; LCSC C191023
J4: Debug; JST_SH_1x03_P1.00mm_Vertical; LCSC C160389
J5: UART; JST_SH_1x03_P1.00mm_Vertical; LCSC C160389
L2: 3.3µH; L_AOTA-B201610_2.0x1.6mm; LCSC C98035
LD1: Blue; LED_0603_1608Metric
LD2: WS2812B-2020; LED_WS2812B-2020_PLCC4_2.0x2.0mm; LCSC C965555
R18, R23: 10K; R_0603_1608Metric; LCSC C2906982
R19, R21, R26: 1K; R_0603_1608Metric; LCSC C21190
R20: 33R; R_0603_1608Metric; LCSC C23140
R22: 0R; R_0603_1608Metric; LCSC C21189
R24, R25: 27R; R_0603_1608Metric; LCSC C25190
R27: 330R; R_0603_1608Metric; LCSC C23138
S3: RP Boot; Button_SMD_3x4x2mm; Mouser Part Number 611-KMR221G-LFS; LCSC C36498961
S4: RP Reset; Button_SMD_3x4x2mm; Mouser Part Number 611-KMR221G-LFS; LCSC C36498961
U4: W25Q128JVPIQ; WSON-8-1EP_6x5mm_P1.27mm_EP3.45x4.35mm; Mouser Part Number 454-W25Q128JVPIQ; LCSC C190862
U5: RP2350; QFN-60-1EP_7x7mm_P0.4mm_EP3.4x3.4mm
U6: APS6404L-3SQR-ZR; PSON50P200X300X50-9N; PARTREV 2.3; LCSC C3040877
Y2: 12 MHz; Crystal_SMD_3225-4Pin_3.2x2.5mm; LCSC C9002

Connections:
+1V1_A: C25.1, C26.1, C28.1, C29.1, L2.1, U5.6 (DVDD), U5.23 (DVDD), U5.39 (DVDD), U5.50 (VREG_FB)
+3V3: C21.1, C22.1, C30.2, C31.1, C32.1, C33.1, C34.1, C35.1, C36.1, C37.1, R18.2, R20.1, R23.2, U4.8 (VCC), U5.1 (IOVDD), U5.11 (IOVDD), U5.20 (IOVDD), U5.30 (IOVDD), U5.38 (IOVDD), U5.44 (ADC_AVDD), U5.45 (IOVDD), U5.49 (VREG_VIN), U5.53 (USB_OTP_VDD), U5.54 (QSPI_IOVDD), U6.8 (VDD); also elsewhere on the board
/RP2350A/BOOT: R21.2, S3.1, S3.3
/RP2350A/D+: R24.1; also elsewhere on the board
/RP2350A/D-: R25.1; also elsewhere on the board
/RP2350A/GPIO0: R23.1, U5.2 (GPIO0), U6.1 (~CE)
/RP2350A/GPIO9: U5.13 (GPIO9); also elsewhere on the board
/RP2350A/GPIO24/UART_1: J5.1, U5.36 (GPIO24)
/RP2350A/GPIO25/UART_3: J5.3, U5.37 (GPIO25)
/RP2350A/GPIO28: U5.42 (GPIO28_ADC2)
/RP2350A/GPIO29: U5.43 (GPIO29_ADC3)
/RP2350A/QSPI_SCLK: U4.6 (CLK), U5.56 (QSPI_SCLK), U6.6 (SCLK)
/RP2350A/QSPI_SD0: U4.5 (DI_(IO0)), U5.57 (QSPI_SD0), U6.5 (SI/SIO(0))
/RP2350A/QSPI_SD1: U4.2 (DO_(IO1)), U5.59 (QSPI_SD1), U6.2 (SO/SIO(1))
/RP2350A/QSPI_SD2: U4.3 (~WP_(IO2)), U5.58 (QSPI_SD2), U6.3 (SIO(2))
/RP2350A/QSPI_SD3: U4.7 (~HOLD_OR_/RESET_(IO3)), U5.55 (QSPI_SD3), U6.7 (SIO(3))
/RP2350A/QSPI_SS: R21.1, R22.1, U5.60 (QSPI_SS)
/RP2350A/SWCLK: J4.3, U5.24 (SWCLK)
/RP2350A/SWD: J4.1, U5.25 (SWD)
/RP2350A/VREG_AVDD: C27.1, R20.2, U5.46 (VREG_AVDD)
/RP2350A/VREG_LX: L2.2, U5.48 (VREG_LX)
/RP2350A/XIN: C23.1, U5.21 (XIN), Y2.3
/RP2350A/XOUT: R19.2, U5.22 (XOUT)
/RP2350/20B/1A/D0: U5.3 (GPIO1); also elsewhere on the board
/RP2350/21B/2A/D1: U5.4 (GPIO2); also elsewhere on the board
/RP2350/22B/3A/D2: U5.5 (GPIO3); also elsewhere on the board
/RP2350/23B/4A/D3: U5.7 (GPIO4); also elsewhere on the board
/RP2350/24B/5A/D4: U5.8 (GPIO5); also elsewhere on the board
/RP2350/25B/6A/D5: U5.9 (GPIO6); also elsewhere on the board
/RP2350/26B/7A/D6: U5.10 (GPIO7); also elsewhere on the board
/RP2350/27B/8A/D7: U5.12 (GPIO8); also elsewhere on the board
/RP2350/29B/10A/VALID: U5.14 (GPIO10); also elsewhere on the board
/RP2350/30B/11A/D0: U5.15 (GPIO11); also elsewhere on the board
/RP2350/31B/12A/D1: U5.16 (GPIO12); also elsewhere on the board
/RP2350/32B/13A/D2: U5.17 (GPIO13); also elsewhere on the board
/RP2350/33B/14A/D3: U5.18 (GPIO14); also elsewhere on the board
/RP2350/34B/15A/D4: U5.19 (GPIO15); also elsewhere on the board
/RP2350/35B/16A/D5: U5.27 (GPIO16); also elsewhere on the board
/RP2350/36B/17A/D6: U5.28 (GPIO17); also elsewhere on the board
/RP2350/37B/18A/D7: U5.29 (GPIO18); also elsewhere on the board
/RP2350/38B/19A/CLK: U5.31 (GPIO19); also elsewhere on the board
/RP2350/39B/20A/VALID: U5.32 (GPIO20); also elsewhere on the board
/RP2350/40B/21A/FS: U5.33 (GPIO21); also elsewhere on the board
/RP2350/41B/22A/DB_MS: U5.34 (GPIO22); also elsewhere on the board
/RP2350/42B/23A/DB_SM: U5.35 (GPIO23); also elsewhere on the board
/RP2350/43B/RUNA/SR: S4.1, S4.3, U5.26 (RUN); also elsewhere on the board
GND: C21.2, C22.2, C23.2, C24.2, C25.2, C26.2, C27.2, C28.2, C29.2, C30.1, C31.2, C32.2, C33.2, C34.2, C35.2, C36.2, C37.2, C38.2, J4.2, J5.2, LD1.1 (K), LD2.2 (VSS), S3.2, S3.4, S4.2, S4.4, U4.4 (GND_1), U4.9 (GND_2), U5.47 (VREG_PGND), U5.61 (GND), U6.4 (VSS), U6.9 (EXP), Y2.2, Y2.4; also elsewhere on the board
unnamed: C24.1, R19.1, Y2.1
unnamed: C38.1, D2.1 (K), LD2.4 (VDD)
unnamed: LD1.2 (A), R26.1
unnamed: LD2.3 (DIN), R27.1
unnamed: R18.1, R22.2, U4.1 (~CS)
unnamed: R26.2, U5.40 (GPIO26_ADC0)
unnamed: R27.2, U5.41 (GPIO27_ADC1)
unnamed: R25.2, U5.51 (USB_DM)
unnamed: R24.2, U5.52 (USB_DP)
VBUS: D2.2 (A); also elsewhere on the board

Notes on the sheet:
44+45
Make sure these are close to RP2350
53+54

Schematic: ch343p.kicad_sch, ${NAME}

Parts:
C92, C93, C94: 100nF; C_0603_1608Metric; LCSC C14663
LD4: Orange; LED_0603_1608Metric; LCSC C965800
R64: 1K; R_0603_1608Metric; LCSC C21190
U20: CH343P; WCH_QFN-16-1EP_3x3mm_P0.5mm_EP1.8x1.8mm; LCSC C2846043

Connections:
+3V3: C94.2, R64.2, U20.1 (VIO); also elsewhere on the board
/CH343P/UD+: U20.7 (UD+); also elsewhere on the board
/CH343P/UD-: U20.8 (UD-); also elsewhere on the board
/ESP_DTR: U20.12 (~DTR); also elsewhere on the board
/ESP_RTS: U20.13 (~RTS); also elsewhere on the board
/TTL_RXD: U20.5 (RXD); also elsewhere on the board
/TTL_TXD: U20.4 (TXD); also elsewhere on the board
GND: C92.1, C93.1, C94.1, U20.2 (GND), U20.17 (GND_EPAD); also elsewhere on the board
unnamed: LD4.2 (A), R64.1
unnamed: LD4.1 (K), U20.10 (~ACT)
unnamed: C93.2, U20.6 (V3_{OUT})
VBUS: C92.2, U20.3 (VDD5), U20.9 (VBUS); also elsewhere on the board

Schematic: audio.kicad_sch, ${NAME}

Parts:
C41, C42, C46, C49, C50: 100nF; C_0603_1608Metric; LCSC C14663
C43, C44: 100uF; C_1206_3216Metric; LCSC C7432784
C45, C47, C48: 10uF; C_0603_1608Metric; LCSC C96446
C51, C52: 1uF; C_0603_1608Metric; LCSC C29936
J7: PJ-320D; AudioJack_3.5mm_PJ320D_AudioOut; LCSC C431535
J8: Speaker; JST_GH_1x02_P1.25mm
L3: 330R 2A; L_0805_2012Metric; LCSC C76819
R33, R34: 4.7K; R_0603_1608Metric; LCSC C23162
R35: 10K; R_0603_1608Metric; LCSC C2906982
U7: TLV320DAC3100IRHBR; Mouser Part Number 595-V320DAC3100IRHBR; LCSC C179677
U8: XC6206P182MR-G; Mouser Part Number 865-XC6206P182MR-G; LCSC C347373

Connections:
+1V8: C42.2, C51.2, U7.3 (DVDD), U8.2 (VOUT)
+3V3: C41.1, C45.2, C46.2, C47.2, C49.2, C52.2, R33.2, R34.2, R35.2, U7.2 (IOVDD), U7.17 (AVDD), U7.28 (HPVDD), U8.3 (VIN); also elsewhere on the board
/Audio/+5V_SPK: C48.2, C50.2, L3.1, U7.21 (SPKVDD_1), U7.24 (SPKVDD_2)
/Audio/SPKM: J8.2, U7.19 (SPKM_1), U7.23 (SPKM_2)
/Audio/SPKP: J8.1, U7.22 (SPKP_1), U7.26 (SPKP_2)
/GPIO2/SDA: R34.1, U7.9 (SDA); also elsewhere on the board
/GPIO3/SCL: R33.1, U7.10 (SCL); also elsewhere on the board
/GPIO8/MCLK: U7.8 (MCLK); also elsewhere on the board
/GPIO9/BCLK: U7.7 (BCLK); also elsewhere on the board
/GPIO10/WCLK: U7.6 (WCLK); also elsewhere on the board
/GPIO11/DIN: U7.5 (DIN); also elsewhere on the board
GND: C41.2, C42.1, C45.1, C46.1, C47.1, C48.1, C49.1, C50.1, C51.1, C52.1, J7.S, U7.1 (IOVSS), U7.16 (AVSS), U7.18 (DVSS), U7.20 (SPKVSS_1), U7.25 (SPKVSS_2), U7.29 (HPVSS), U7.33 (EP), U8.1 (VSS); also elsewhere on the board
unnamed: C43.1, J7.R
unnamed: C44.1, J7.T
unnamed: C44.2, U7.27 (HPL)
unnamed: C43.2, U7.30 (HPR)
unnamed: R35.1, U7.31 (~RESET)
VBUS: L3.2; also elsewhere on the board
